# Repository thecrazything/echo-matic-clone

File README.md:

# Echo-matic
The Echo-matic is a small DIY project that enables you to use an old three-head tape deck as an analog delay.
Effectivley it is a simple mixer that takes an input, sends it to a tape deck, then retrives the signal back and re-mixes it with the original signal. It has some controls for wet/dry mix, level and echo repeats.

This project was made from the information found in this blog: https://proto-schlock.blogspot.com/2015/04/echo-matic-diy-tape-delay.html

## Original article
This is the original article that this project is based on. It contains a BOM, a diagram and a circuit.

## Disclaimer
This circuitboard is currently untested.

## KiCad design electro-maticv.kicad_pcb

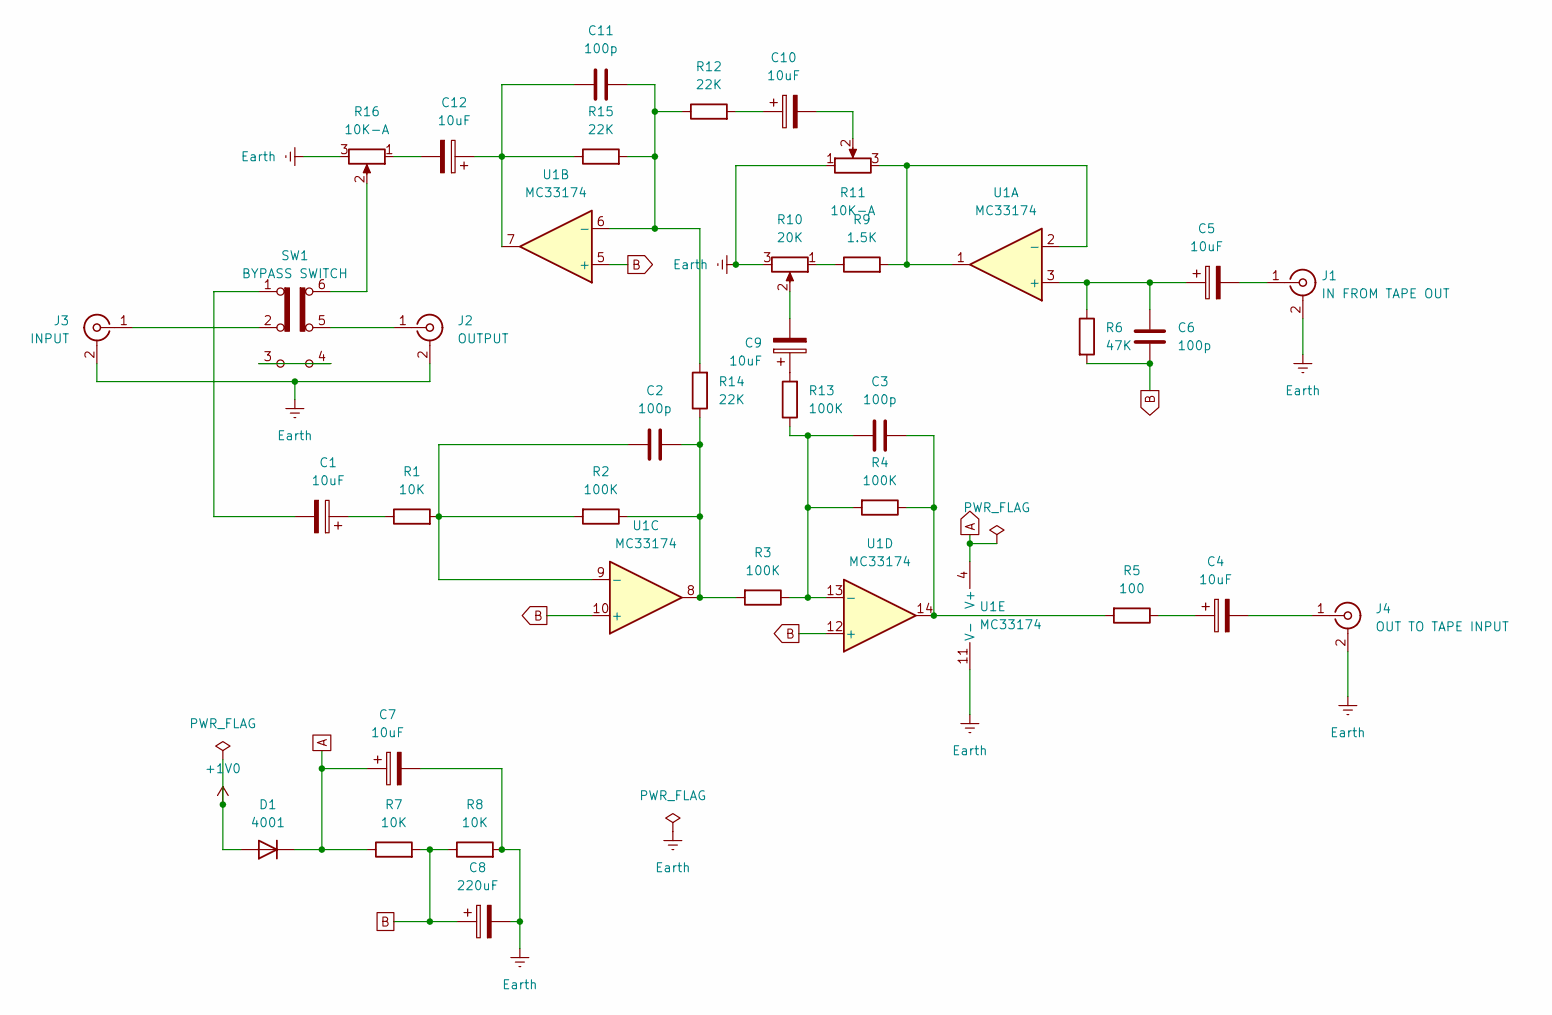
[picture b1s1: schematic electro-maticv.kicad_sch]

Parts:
C1, C4, C5, C7, C9, C10, C12: 10uF; CP_Radial_D5.0mm_P2.00mm
C2, C3, C6, C11: 100p; C_Disc_D3.0mm_W2.0mm_P2.50mm
C8: 220uF; CP_Radial_D6.3mm_P2.50mm
D1: 4001; D_DO-41_SOD81_P7.62mm_Horizontal
J1: IN FROM TAPE OUT; PinHeader_1x02_P2.54mm_Vertical
J2: OUTPUT; PinHeader_1x02_P2.54mm_Vertical
J3: INPUT; PinHeader_1x02_P2.54mm_Vertical
J4: OUT TO TAPE INPUT; PinHeader_1x02_P2.54mm_Vertical
R1, R7, R8: 10K; R_Axial_DIN0309_L9.0mm_D3.2mm_P2.54mm_Vertical
R2, R3, R4, R13: 100K; R_Axial_DIN0309_L9.0mm_D3.2mm_P2.54mm_Vertical
R5: 100; R_Axial_DIN0309_L9.0mm_D3.2mm_P2.54mm_Vertical
R6: 47K; R_Axial_DIN0309_L9.0mm_D3.2mm_P2.54mm_Vertical
R9: 1.5K; R_Axial_DIN0309_L9.0mm_D3.2mm_P2.54mm_Vertical
R10: 20K; PinHeader_1x03_P2.54mm_Vertical
R11, R16: 10K-A; PinHeader_1x03_P2.54mm_Vertical
R12, R14, R15: 22K; R_Axial_DIN0309_L9.0mm_D3.2mm_P2.54mm_Vertical
SW1: BYPASS SWITCH; SW_CK_JS202011CQN_DPDT_Straight
U1: MC33174; DIP-14_W7.62mm_Socket

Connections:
+1V0: D1.2 (A)
A: C7.1, D1.1 (K), R7.1, U1.4 (V+)
B: C6.2, C8.1, R6.2, R7.2, R8.1, U1.5 (+), U1.10 (+), U1.12 (+)
Earth: C7.2, C8.2, J1.2 (Ext), J2.2 (Ext), J3.2 (Ext), J4.2 (Ext), R8.2, R10.3, R11.1, R16.3, U1.11 (V-)
unnamed: C1.1, R1.1
unnamed: C1.2, SW1.1 (A)
unnamed: C2.2, R2.1, R3.2, R14.1, U1.8
unnamed: C3.2, R4.1, R5.2, U1.14
unnamed: C4.1, R5.1
unnamed: C9.1, R13.2
unnamed: C9.2, R10.2
unnamed: C10.1, R12.2
unnamed: C10.2, R11.2
unnamed: C11.1, C12.1, R15.1, U1.7
unnamed: C12.2, R16.1
unnamed: C5.2, J1.1 (In)
unnamed: J2.1 (In), SW1.5 (B)
unnamed: J3.1 (In), SW1.2 (B)
unnamed: C4.2, J4.1 (In)
unnamed: R9.1, R10.1
unnamed: R16.2, SW1.6 (C)
unnamed: SW1.3 (C), SW1.4 (A)
unnamed: C5.1, C6.1, R6.1, U1.3 (+)
unnamed: R9.2, R11.3, U1.1, U1.2 (-)
unnamed: C11.2, R12.1, R14.2, R15.2, U1.6 (-)
unnamed: C2.1, R1.2, R2.2, U1.9 (-)
unnamed: C3.1, R3.1, R4.2, R13.1, U1.13 (-)

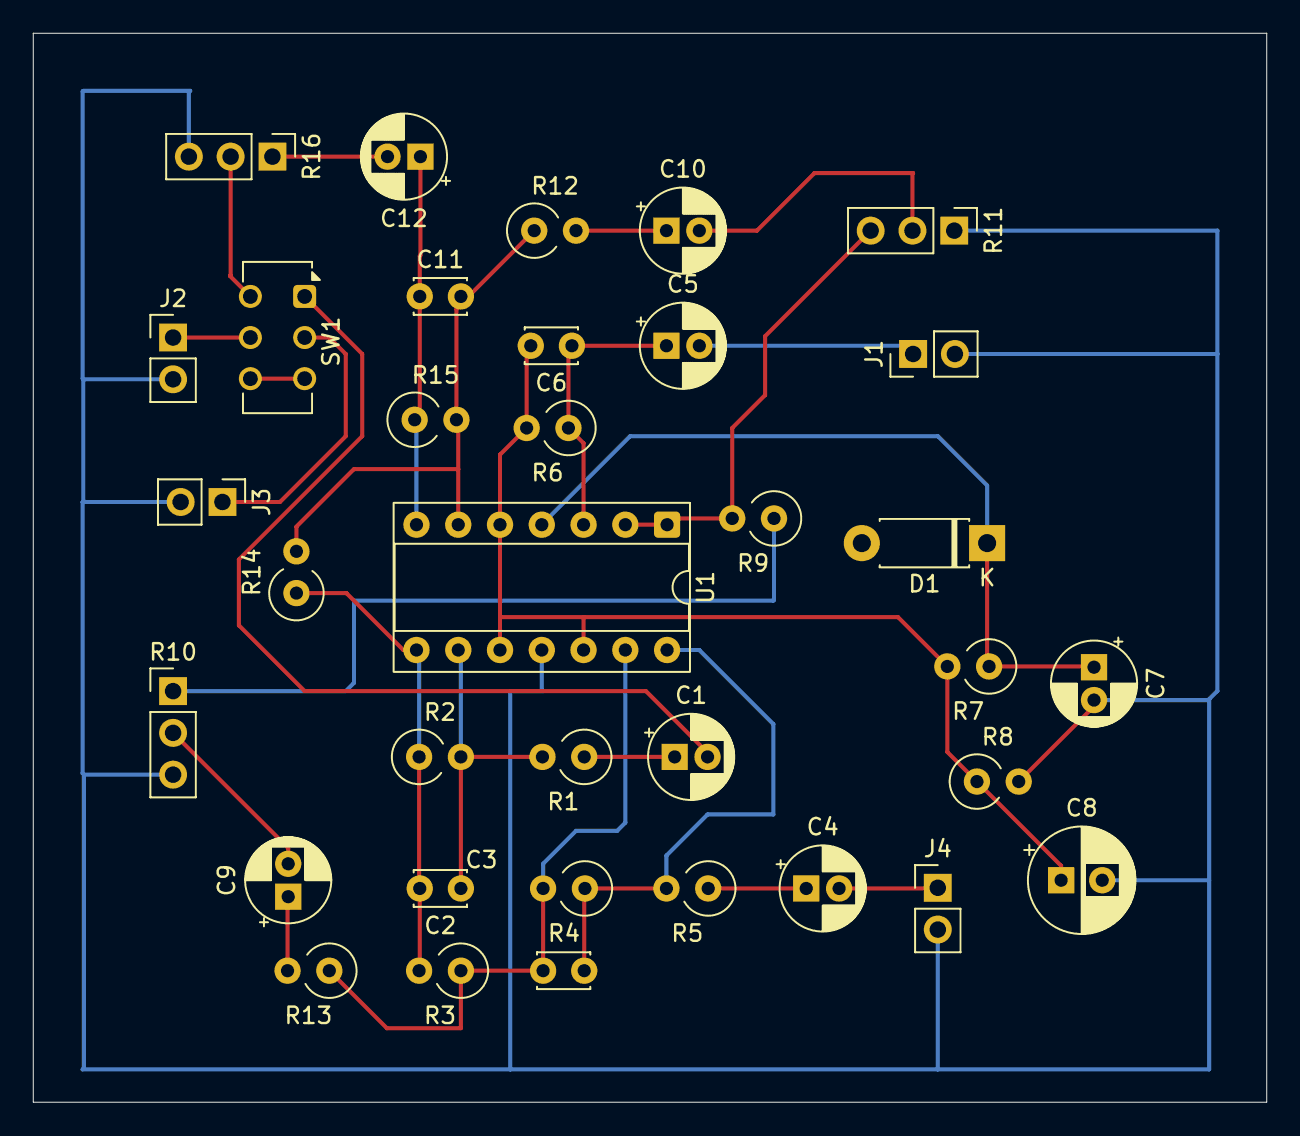
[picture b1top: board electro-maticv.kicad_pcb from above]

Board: 2 copper layers, 75.0 x 65.0 mm, 35 parts (0 on the bottom side), 26 nets.

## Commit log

2025-04-22 stuff
2025-04-22 removed ignored files
